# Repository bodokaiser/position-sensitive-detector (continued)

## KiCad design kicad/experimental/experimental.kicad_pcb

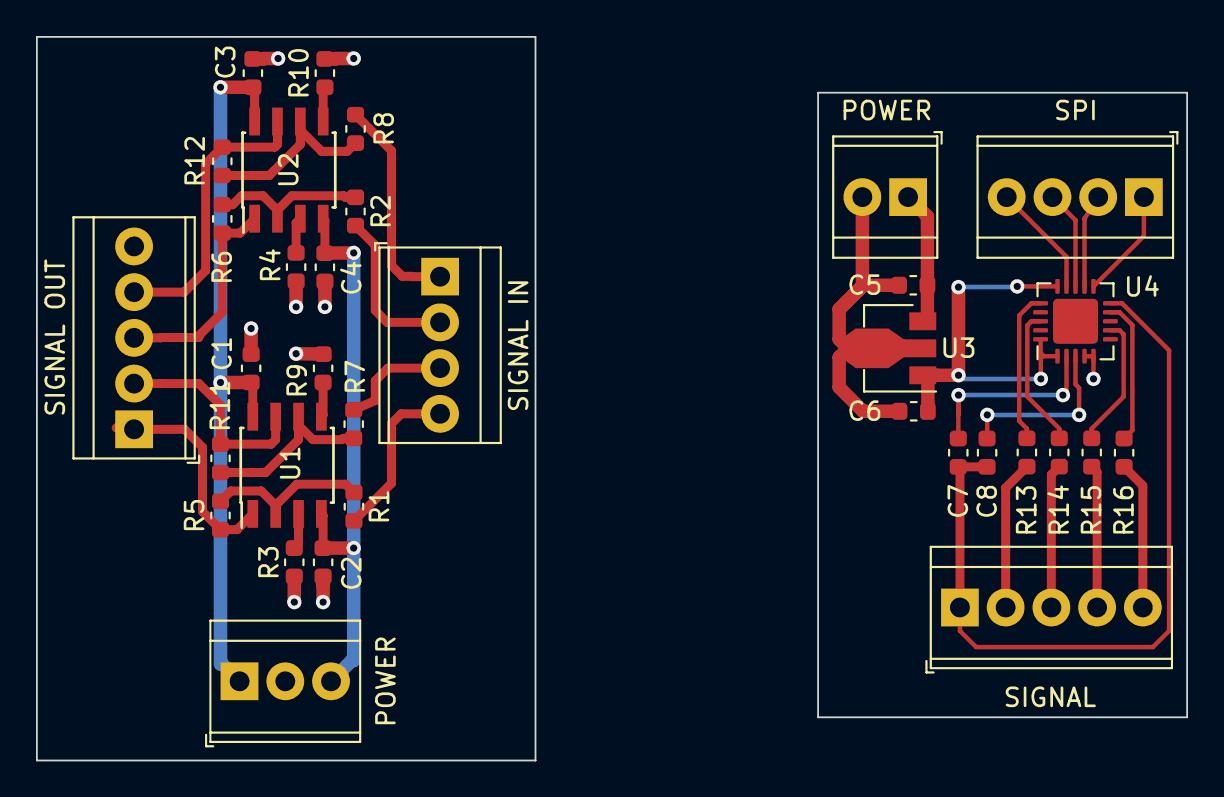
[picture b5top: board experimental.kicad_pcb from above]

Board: 2 copper layers, 63.9 x 40.2 mm, 34 parts (0 on the bottom side), 35 nets.

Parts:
C1, C2, C3, C4, C6, C8: 100n; C_0603_1608Metric
C5: 330n; C_0603_1608Metric
C7: 10u; C_0603_1608Metric
POWER: PWR_IN; TerminalBlock_TE_282834-2_1x02_P2.54mm_Horizontal
POWER#2: PWR_IN; TerminalBlock_TE_282834-3_1x03_P2.54mm_Horizontal
R1, R2, R3, R4, R7, R8, R9, R10: 3k; R_0603_1608Metric
R5, R6, R11, R12: 1k; R_0603_1608Metric
R13, R14, R15, R16: 100; R_0603_1608Metric
SIGNAL: SIG_IN; TerminalBlock_TE_282834-5_1x05_P2.54mm_Horizontal
SIGNAL IN: SIG_IN; TerminalBlock_TE_282834-4_1x04_P2.54mm_Horizontal
SIGNAL OUT: SIG_OUT; TerminalBlock_TE_282834-5_1x05_P2.54mm_Horizontal
SPI: SPI; TerminalBlock_TE_282834-4_1x04_P2.54mm_Horizontal
U1, U2: OPA2197; SOIC-8_3.9x4.9mm_P1.27mm
U3: L78L05; SOT-89-3
U4: AD7682BCP; LFCSP-20-1EP_4x4mm_P0.5mm_EP2.5x2.5mm

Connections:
+5V: C6.1, U3.1, U4.1, U4.15, U4.20
+15V: C1.1, C3.1, C5.1, POWER.1, POWER#2.1, U1.8, U2.8, U3.3
-15V: C2.1, C4.1, POWER#2.3, U1.4, U2.4
/ADC/CNV: SPI.1, U4.11
/ADC/DIN: SPI.2, U4.12
/ADC/IN0: R13.1, U4.16
/ADC/IN1: R14.1, U4.18
/ADC/IN2: R15.1, U4.7
/ADC/IN3: R16.1, U4.9
/ADC/SCK: SPI.3, U4.13
/ADC/SDO: SPI.4, U4.14
/ADC/X1: R13.2, SIGNAL.2
/ADC/X2: R14.2, SIGNAL.3
/ADC/Y1: R15.2, SIGNAL.4
/ADC/Y2: R16.2, SIGNAL.5
/BUFFER/IN_X1: R1.2, SIGNAL IN.4
/BUFFER/IN_X2: R7.2, SIGNAL IN.3
/BUFFER/IN_Y1: R2.2, SIGNAL IN.2
/BUFFER/IN_Y2: R8.2, SIGNAL IN.1
/BUFFER/OUT_X1: R5.1, SIGNAL OUT.1, U1.1
/BUFFER/OUT_X2: R11.1, SIGNAL OUT.2, U1.7
/BUFFER/OUT_Y1: R6.1, SIGNAL OUT.3, U2.1
/BUFFER/OUT_Y2: R12.1, SIGNAL OUT.4, U2.7
GND: C1.2, C2.2, C3.2, C4.2, C5.2, C6.2, POWER.2, POWER#2.2, R3.2, R4.2, R9.2, R10.2, SIGNAL OUT.5, U3.2, U4.4, U4.5
GNDA: C7.2, C8.2, SIGNAL.1, U4.10
unnamed: C7.1, U4.2
unnamed: C8.1, U4.3
unnamed: R1.1, R5.2, U1.2
unnamed: R2.1, R6.2, U2.2
unnamed: R3.1, U1.3
unnamed: R4.1, U2.3
unnamed: R9.1, U1.5
unnamed: R10.1, U2.5
unnamed: R7.1, R11.2, U1.6
unnamed: R8.1, R12.2, U2.6

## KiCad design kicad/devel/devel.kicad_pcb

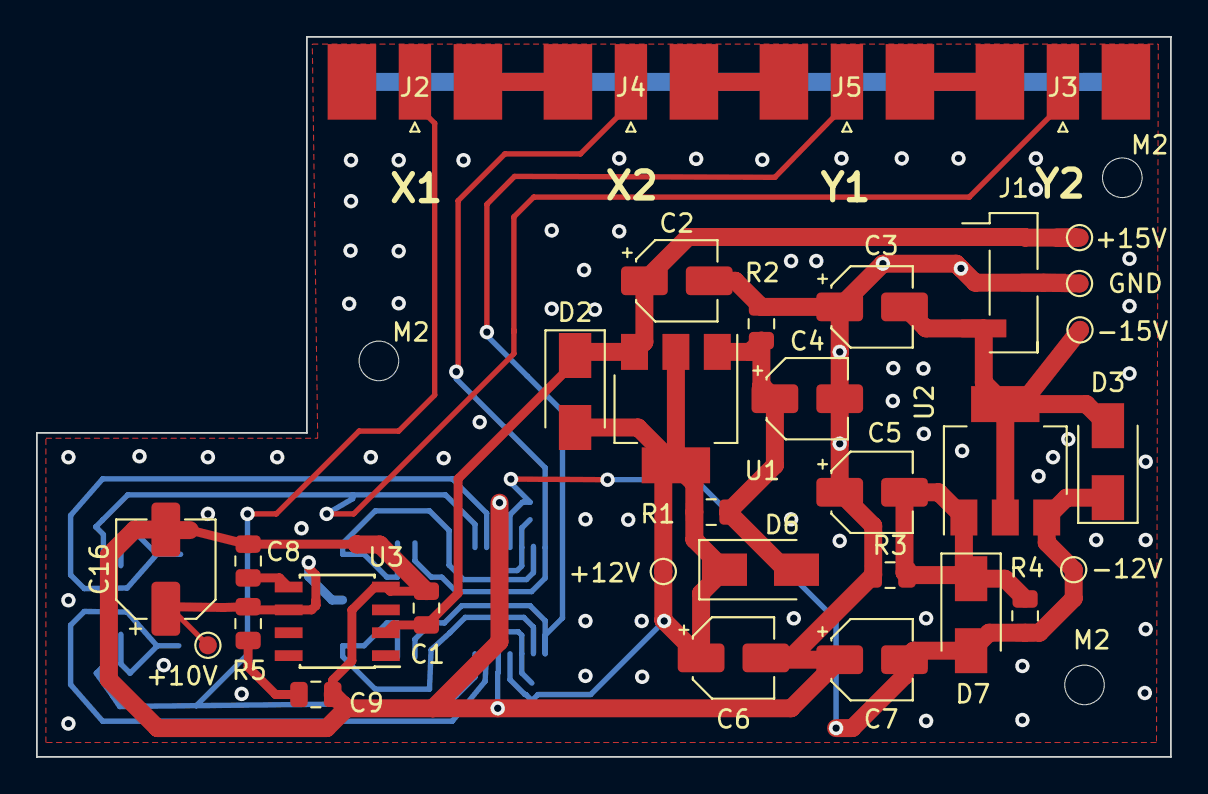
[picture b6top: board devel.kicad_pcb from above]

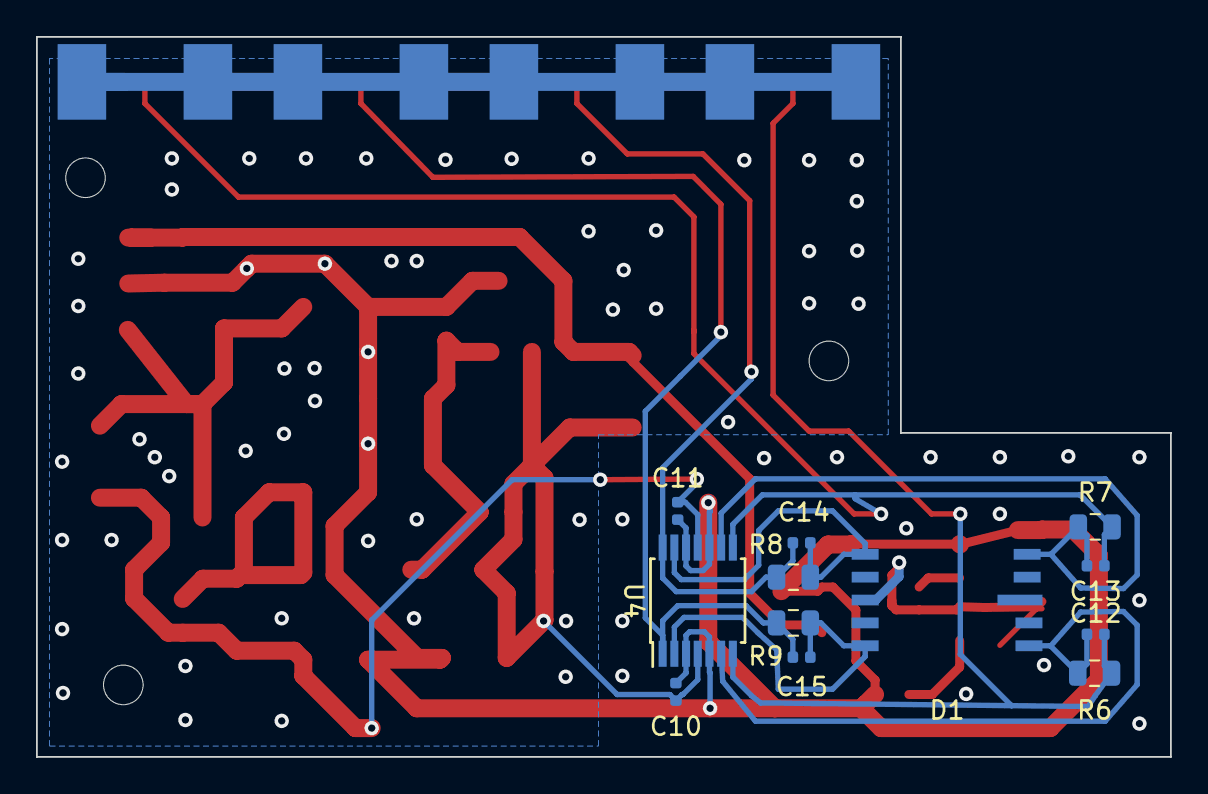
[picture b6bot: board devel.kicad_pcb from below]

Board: 4 copper layers, 63.0 x 40.0 mm, 48 parts (12 on the bottom side), 18 nets.

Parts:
+10V: +10V; TestPoint_Pad_D1.0mm
+12V: +12V; TestPoint_Pad_D1.0mm
+15V: +15V; TestPoint_Pad_D1.0mm
-12V: -12V; TestPoint_Pad_D1.0mm
-15V: -15V; TestPoint_Pad_D1.0mm
C1, C8: 1u; C_0805_2012Metric
C2, C3: 0.1u; CP_Elec_4x5.4
C4, C5: 10u; CP_Elec_4x3.9
C6, C7: 1u; CP_Elec_4x3.9
C9: 10n; C_0805_2012Metric
C10, C11: 100n; C_0402_1005Metric
C12, C13, C14, C15: 4p; C_0402_1005Metric
C16: 22u; CP_Elec_5x5.3
D1: S599x; S5990
D2, D3, D6, D7: S1A; D_SMA
GND: GND; TestPoint_Pad_D1.0mm
J1: CONN_PWR; PinHeader_1x03_P2.54mm_Vertical_SMD_Pin1Left
J2: CONN_X1; SMA_Molex_73251-2120_EdgeMount
J3: CONN_Y2; SMA_Molex_73251-2120_EdgeMount
J4: CONN_X2; SMA_Molex_73251-2120_EdgeMount
J5: CONN_Y1; SMA_Molex_73251-2120_EdgeMount
M2, M2#2, M2#3: MountingHole_2.2mm_M2
R1, R4: 120; R_0805_2012Metric
R2, R3: 1k; R_0805_2012Metric
R5: 100; R_0805_2012Metric
R6, R7, R8, R9: 100k; R_0805_2012Metric
U1: LM317_SOT223; SOT-223-3_TabPin2
U2: LM337_SOT223; SOT-223-3_TabPin2
U3: REF5010IDGK; SOIC-8_3.9x4.9mm_P1.27mm
U4: OPA4197; TSSOP-14_4.4x5mm_P0.65mm

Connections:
+12V: +12V.1, C6.1, C10.2, D2.2, D6.1, R1.1, U1.2, U4.4
+15V: +15V.1, C1.1, C2.1, D2.1, J1.1, U1.3, U3.2
-12V: -12V.1, C7.2, C11.2, D3.1, D7.2, R4.2, U2.3, U4.11
-15V: -15V.1, C3.2, D3.2, J1.3, U2.2
GND: C1.2, C2.2, C3.1, C4.2, C5.1, C6.2, C7.1, C8.2, C9.2, C10.1, C11.1, C16.2, GND.1, J1.2, J2.2, J3.2, J4.2, J5.2, R2.2, R3.1, U3.4, U4.3, U4.5, U4.10, U4.12
unnamed: C4.1, D6.2, R1.2, R2.1, U1.1
unnamed: C5.2, D7.1, R3.2, R4.1, U2.1
unnamed: C8.1, U3.5
unnamed: C9.1, R5.2
unnamed: C12.1, D1.1, R6.1, U4.6
unnamed: C12.2, J2.1, R6.2, U4.7
unnamed: C13.1, D1.5, R7.1, U4.9
unnamed: C13.2, J3.1, R7.2, U4.8
unnamed: C14.1, D1.6, R8.1, U4.13
unnamed: C14.2, J4.1, R8.2, U4.14
unnamed: C15.1, D1.10, R9.1, U4.2
unnamed: C15.2, J5.1, R9.2, U4.1
unnamed: +10V.1, C16.1, D1.8, R5.1, U3.6

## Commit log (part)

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2019-02-19 started schematic of amplifier
2019-02-19 completed difference and summation stages
2019-02-19 redesigned blocks for space efficiency
2019-02-23 added LTSpice simulation files
2019-02-23 renamed opamp.asc to amp.asc
2019-02-26 added calculation notebook, renamed repository
2019-02-26 rewrote preamp ltspice simulation
2019-02-26 rewrote schematics
2019-03-02 updated simulation circuits, replaced notebook with latex
2019-03-03 completed position-sensitive-detector section of the documentation
2019-03-03 started with analogue-signal-processing section
2019-03-04 added preamp calculation notebook
2019-03-04 renamed Photodiode kicad library to Library
2019-03-05 added voltage regulator to schematic
2019-03-05 redesigned psd + preamp block in schematic
2019-03-09 added optional offset compensation to preamplifiers
2019-03-09 updated schematic title, company
2019-03-09 added total summing amplifier
2019-03-09 added test points to circuit
2019-03-11 updated calculation notebooks
2019-03-12 updated signal calculation notebook
2019-03-12 completed photodiode signal-to-noise
2019-03-20 replaced ltspice simulations
2019-03-20 removed offset compensation, added bias voltage to schematic
2019-03-20 updated schematics
2019-03-20 extended circuit sheet size to A3, added connectors
2019-03-21 added analog divider and connectors
2019-03-21 renamed X,Y to POSX, POSY
2019-03-21 replaced reverse bias voltage regulator with voltage reference
2019-03-21 redrew schematic for improved readability, fixed output buffers
2019-03-22 redrew schematic with kicad 5.1 without corrupted library
2019-03-22 converted schematic to flat hierarchical
2019-03-22 separated symbol library according to functionality
2019-03-22 redesigned S599x symbol according to symbol guidelines
2019-03-22 fixed opamp supply voltage polarisation, fixed output buffers
2019-03-22 fixed floating buffer in arthimetic unit
2019-03-27 fixed arithmetic typo, decoupling cap polarisation
2019-03-27 removed arithmetic unit from development board, changed output connectors
2019-03-27 made small adjustments, created netlist
2019-03-27 removed inverting output opamps
2019-03-27 assigned footprints to symbols
2019-03-27 created S5990 footprint, created pcb layout
2019-03-28 merged circuit sheets to single sheet, removed extra diodes, changed diode type
2019-03-28 created first pcb layout draft
2019-03-29 simplified circuit schematic, used uniform resistor footprints
2019-03-29 completed sublayout of detector and preamp
2019-03-29 completed sublayout of bias voltage reference
2019-03-29 added mosfet polarity protection to power connector
2019-03-29 added protection diodes to supply voltage regulators
2019-03-29 fixed details in power connector circuit
2019-03-29 updated footprint assignment
2019-03-30 completed sublayout of power input
2019-03-30 completed pcb sublayouts
2019-03-30 retraced regulators according to datasheet layout
2019-03-30 moved sublayouts around
2019-04-01 created custom sma footprints
2019-04-01 completed pcb layout routing
2019-04-01 replaced sma connector footprint
2019-04-01 completed pcb layout with cooper fills
2019-04-02 updated pcb layout, added screws
2019-04-03 added preamp-offset ltspice simulation
2019-04-03 realigned vias, added silk labels
2019-04-03 restructured documentation
2019-04-03 added power management section to documentation
2019-04-04 added input bias, offset circuit for opamp, rewrote transimpedance circuit
2019-04-04 updated transimpedance figures, added books to literature
2019-04-04 added circuits and equations for op amp input current
2019-04-04 added input offset voltage compensation circuit
2019-04-06 updated transimpedance amplifier section
2019-04-06 cleaned up documentation, removed uncertain sections
2019-04-06 wrote intro for preamplifier section
2019-04-06 completed basic design in preamplifier section
2019-04-06 updated input offset voltage subsection in preamplifier section
2019-04-08 completed input offset voltage subsection in preamplifier section
2019-04-08 fixed mistakes in the input offset voltage subsection of the preamplifier section
2019-04-08 completed input bias currents subsection in the preamplifier section
2019-04-08 completed stability and bandwidth section in preamplifier
2019-04-09 added requirements section to documentation
2019-04-09 added some figures to detector section of documentation
2019-04-13 added detector references, pn junction figures to detector section
2019-04-15 added pn junction figures to detector section
2019-04-15 added reverse biased potential figure to detector
2019-04-15 updated junction figures in detector section
2019-04-15 added junction under illumination figure to detector section
2019-04-15 reduced energy gap in reverse biased figures in detector section
2019-04-16 added iv characteristics to detector section
2019-04-16 added content todos to complete detector section
2019-04-16 added contact configuration figure to detector section
2019-04-17 completed lateral equations in detector section
2019-04-17 completed lateral photodiode subsection in detector section
2019-04-18 completed detector section
2019-04-22 added power supply filter to documentation
2019-04-23 added voltage regulator circuit to power section
2019-04-23 added voltage reference circuit to power section
2019-04-25 removed notebooks, updated folder structure
2019-04-25 restructured documentation, moved theory to appendix
2019-04-25 moved tex source for figures to separate files
2019-04-25 added todo comments to documentation
2019-04-25 removed old scheets, updated symbol paths
2019-04-30 started modular PCB design
2019-07-30 created modular project with schematic and shield component
2019-07-30 removed signal shield from power module, updated page settings
2019-07-31 completed header footprint, started with pcb design of power board
2019-07-31 completed pcb design of power board
2019-07-31 updated detector board footprints, added edge cuts
2019-08-01 completed detector board
2019-08-01 started redesign of pcb
2019-08-01 redesigned pcb with more symmetry
2019-08-02 applied pcb design suggestions to modular boards
2019-08-02 removed overlap of component labels in modular boards
2019-08-02 fixed opamp input terminal connection, connected some caps directly to gnd through vias
2019-08-05 via stitched gnd trace of voltage reference, added zones around voltage regulators
2019-08-10 added arithmetic board to modular design
2019-08-14 completed schematic of arthimetic board
2019-08-23 added pcb design of arithmetic board
2019-08-23 updated arithmetic schematic with resistor arrays and dual opamp, removed old footprints
2019-08-23 applied pcb design feedback to arithmetic board
2019-08-23 created experimental project
2019-08-25 removed current adc components from experimental kicad design
2019-08-26 realigned reference labels on arithmetic pcb
2019-08-26 added resistors to analog inputs of adc
2019-09-25 fixed generic opamp symbol pin layout, updated pcb of arithmetic board
2019-09-26 added test points to experimental adc and buffer boards, improved schematic, assigned footprints
2019-09-26 designed pcb for experimental buffer board
2019-09-26 completed pcb design of experimental buffer and adc
2020-01-31 removed ltspice folder and old kicad files
2020-01-31 started schematic of revision 2.0.0
2020-01-31 completed schematic of revision 2.0.0
2020-01-31 removed latex includes and LICENSE.md, renamed project
2020-02-02 assignd footprints to schematic, grouped footprints in pcb designer
2020-02-06 updated footprints of S5990, OPA197 and OPA2197
2020-02-06 updated S5990 symbol to show pin number
2020-02-06 removed 2.0.0 kicad rescue files
2020-02-10 grouped components for 2.0.0 design on pcb
2020-02-15 separated 2.0.0 using hierarchical sheets, added voltage reference to 2.0.0
2020-02-15 added power leds and test points to 2.0.0
2020-03-19 replaced OPAx197s with standard library symbols, increased voltage regulator caps
2020-03-19 created extra projects for arithmetic and detector sheet
2020-03-19 removed 2.0.0 project
2020-03-19 assigned footprints to detector schema, created detector pcb file
2020-03-19 grouped components of detector 2.0.0 pcb
2020-03-20 routed REF5010 tracks for 2.0.0 detector board
2020-03-20 routed tracks for LM317 on 2.0.0 detector
2020-03-20 completed tracks of voltage references and regulators of 2.0.0 detector
2020-03-20 replaced voltage regulators of 2.0.0 detector with LDO regulators
    Low-dropout (LDO) voltage regulators come in small packages, i.e.
    SOT-23, however they are more susceptible for ringing.
    The packages in which you can buy the non-LDO voltage regulators, e.g. SOIC-8 or SOT-223,
    are large compared to the remaining circuitry.
2020-03-20 placed testpoints on pcb for 2.0.0 detector
2020-03-20 added LT1761, LT1964 and Kingbright LED datasheets
2020-03-28 created common symbol and footprint library, completed placement of components of 2.0.0 detector
2020-03-28 completed arithmetic 2.0.0 schematic, associated footprints
2020-03-28 added first attempt for the 2.0.0 arithmetic pcb design
2020-04-12 routed traces for 2.0.0 pcbs
2020-04-13 replaced dual op-amp on 2.0.0 arithmetic board with two op-amps
2020-04-14 improved arithmetic 2.0.0 pcb
2020-04-14 completed arithmetic 2.0.0 pcb
2020-04-15 reworked detector 2.0.0 pcb
2020-04-17 completed redesign of arithmetic and detector 2.0.0 boards
2020-04-17 removed kicad/1.0.0, moved kicad/2.0.0 to kicad, using git tags for release
2020-04-17 applied ground-poor, via-stitching, added logo and rev to boards
2020-04-20 disabled fill zones, removed vias
2020-04-20 reduced trace width to 0.5 mm
2020-04-20 fixed signal routing, remaining vias, large traces
2020-04-20 added fill zones around voltage regulators
2020-04-21 re-routed traces on arithmetic board
2020-04-22 move detector power supplies around (wip)
2020-04-24 added BOM.xlsx and kicad HTML bom plugin export
2020-04-24 added mounting holes to eeschema, replaced mounting holes with pad
2020-04-24 changed header shield pins for improved detector routing
2020-04-25 redesigned detector pcb
2020-04-25 removed some vias from detector pcb
2020-04-25 adjusted arithmetic pcb for updated detector pcb
2020-04-28 added links for not-stocked components in BOM.xlsx
2020-05-05 fix some DRC errors, remove some test points
2020-05-13 applied suggestions from Bodo Hecker
    * changed R23 to 2k
    * replaced pin holes in detector with padded pin holes
    * increased casing of led resistors to 1210
2020-10-01 updated file structure and latex sections
2020-10-01 added electrical testing section to documentation
2020-10-02 updated latex structure, included old sections
2020-10-03 updated voltage regulator circuit figure
2020-10-03 updated voltage reference circuit figure
2020-10-03 added arithmetic amplifier circuit to schematic section
2020-10-04 updated photodiode frontend subsection in schematic section
2020-10-04 updated voltage regulator subsection in schematic section
2020-10-04 updated arithmetic amplifier subsection in schematic section
2020-10-04 updated file and section structure of previous manufacturing, commissioning, and testing sections
2020-10-04 added kicad screenshots to commissioning subsection
2020-10-04 restructured manufacturing and testing subsections in production section
2020-10-05 renamed usage to measurement, added electrical and optical setup subsections to measurement section
2020-10-06 completed and renamed debugging guidelines appendix to troubleshooting
2020-10-06 reworked position-sensitive photodiode section with Grammarly
2020-10-06 reworked opertional amplifier section with Grammarly
2020-10-06 fixed bibliography setup
2020-10-07 replaced measurements, updated analysis notebook
2020-10-07 completed analysis notebook
2020-10-07 added figures, equations, and tables to measurement section
2020-10-08 merged measurment plots into voltages and positions
2020-10-08 completed measurement section, replaced eqref with cref
2020-10-08 corrected for Bodo Hecker\'s suggestions
